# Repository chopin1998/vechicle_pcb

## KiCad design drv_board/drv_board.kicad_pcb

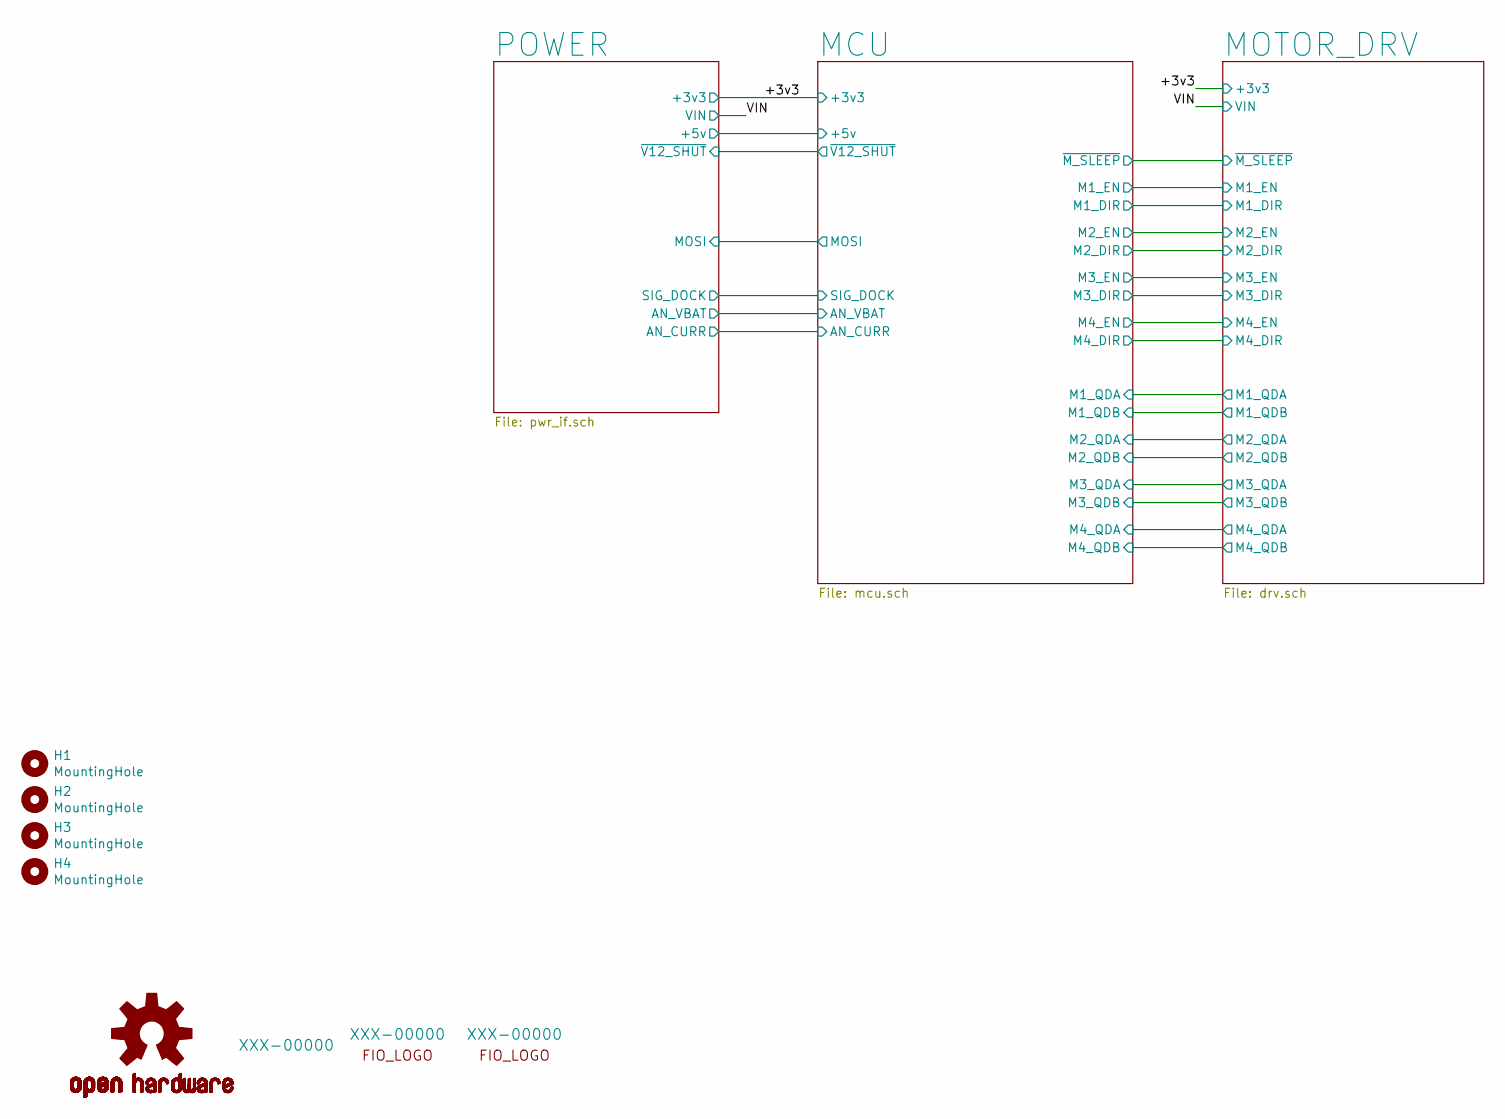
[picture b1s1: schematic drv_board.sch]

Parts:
H1, H2, H3, H4: MountingHole; MountingHole_3.2mm_M3_ISO14580
LOGO1: OSHW-LOGOL; OSHW-Logo2_7.3x6mm_SilkScreen
LOGO2: FIO_LOGOV2; KiCad-Logo2_5mm_SilkScreen
LOGO3: FIO_LOGOV2; ESD-Logo_6.6x6mm_SilkScreen

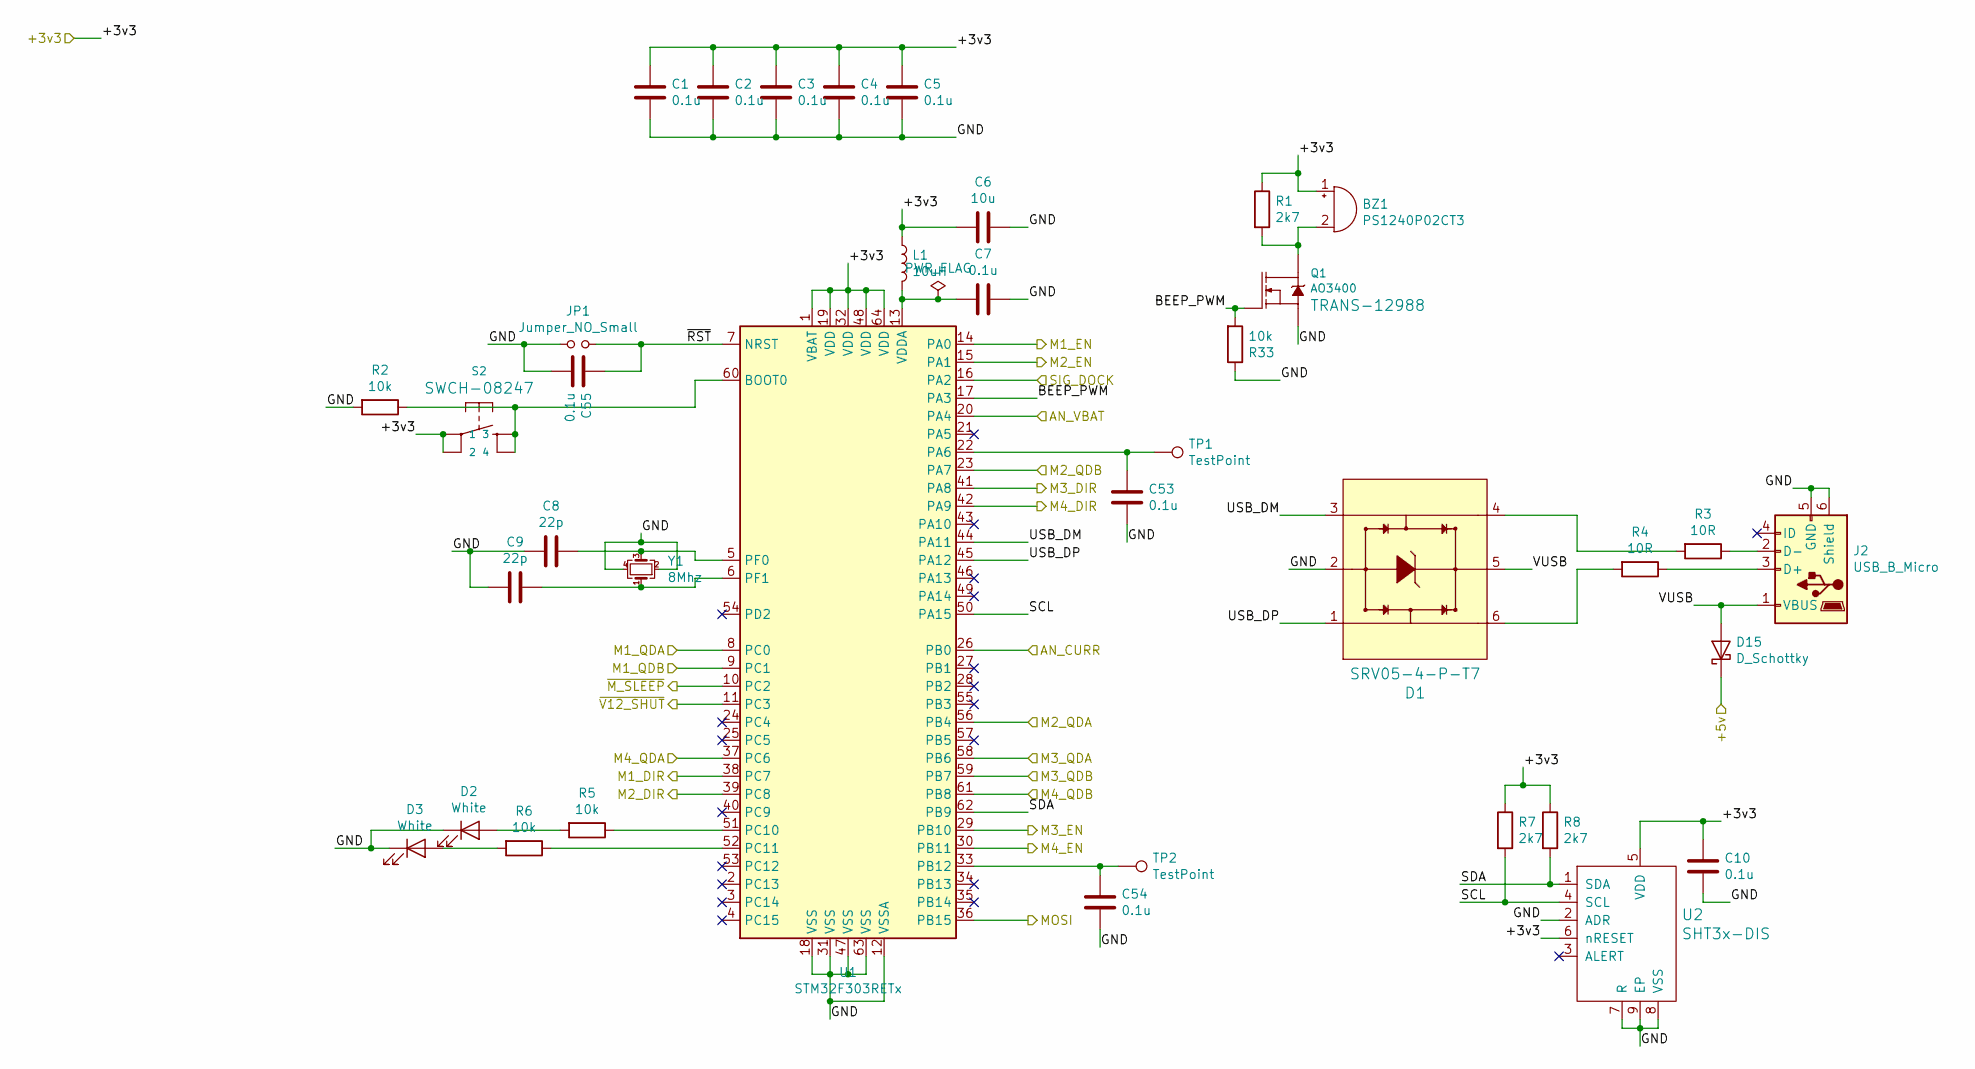
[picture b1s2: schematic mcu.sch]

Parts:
BZ1: PS1240P02CT3; Buzzer_12x9.5RM7.6
C1, C2, C3, C4, C5, C7, C10, C53, C54, C55: 0.1u; C_0402_1005Metric
C6: 10u; C_0402_1005Metric
C8, C9: 22p; C_0402_1005Metric
D1: SRV05-4-P-T7; SOT23-6L; MPN USBLC6-2SC6; Digi-Key_PN 497-5235-1-ND
D2, D3: White; LED_0603_1608Metric
D15: D_Schottky; D_SOD-123F
J2: USB_B_Micro; USB_Micro-B_Wuerth_629105150521
JP1: Jumper_NO_Small; PinHeader_1x02_P1.27mm_Vertical
L1: 10uH; L_0603_1608Metric
Q1: AO3400; SOT-23
R1, R7, R8: 2k7; R_0402_1005Metric
R2, R5, R6, R33: 10k; R_0402_1005Metric
R3, R4: 10R; R_0402_1005Metric
S2: MOMENTARY-SWITCH-SPST-2-SMD-5.2MM; TACTILE_SWITCH_SMD_5.2MM
TP1, TP2: TestPoint; TestPoint_Pad_D1.0mm
U1: STM32F303RETx; LQFP-64_10x10mm_P0.5mm
U2: SHT3x-DIS; DFN-8-1EP_2x2mm_P0.5mm_EP0.9x1.5mm
Y1: 8Mhz; Crystal_SMD_SeikoEpson_TSX3225-4Pin_3.2x2.5mm

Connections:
/+3v3: BZ1.1 (-), C1.1, C2.1, C3.1, C4.1, C5.1, C6.2, C10.1, L1.1, R1.1, R7.1, R8.1, S2.1, S2.2, U1.1 (VBAT), U1.19 (VDD), U1.32 (VDD), U1.48 (VDD), U1.64 (VDD), U2.5 (VDD), U2.6 (nRESET); also elsewhere on the board
/MCU/+5v: D15.1 (K); also elsewhere on the board
/MCU/AN_CURR: U1.26 (PB0); also elsewhere on the board
/MCU/AN_VBAT: U1.20 (PA4); also elsewhere on the board
/MCU/BEEP_PWM: Q1.1 (G), R33.2, U1.17 (PA3)
/MCU/M1_DIR: U1.38 (PC7); also elsewhere on the board
/MCU/M1_EN: U1.14 (PA0); also elsewhere on the board
/MCU/M1_QDA: U1.8 (PC0); also elsewhere on the board
/MCU/M1_QDB: U1.9 (PC1); also elsewhere on the board
/MCU/M2_DIR: U1.39 (PC8); also elsewhere on the board
/MCU/M2_EN: U1.15 (PA1); also elsewhere on the board
/MCU/M2_QDA: U1.56 (PB4); also elsewhere on the board
/MCU/M2_QDB: U1.23 (PA7); also elsewhere on the board
/MCU/M3_DIR: U1.41 (PA8); also elsewhere on the board
/MCU/M3_EN: U1.29 (PB10); also elsewhere on the board
/MCU/M3_QDA: U1.58 (PB6); also elsewhere on the board
/MCU/M3_QDB: U1.59 (PB7); also elsewhere on the board
/MCU/M4_DIR: U1.42 (PA9); also elsewhere on the board
/MCU/M4_EN: U1.30 (PB11); also elsewhere on the board
/MCU/M4_QDA: U1.37 (PC6); also elsewhere on the board
/MCU/M4_QDB: U1.61 (PB8); also elsewhere on the board
/MCU/MOSI: U1.36 (PB15); also elsewhere on the board
/MCU/SCL: R7.2, U1.50 (PA15), U2.4 (SCL)
/MCU/SDA: R8.2, U1.62 (PB9), U2.1 (SDA)
/MCU/SIG_DOCK: U1.16 (PA2); also elsewhere on the board
/MCU/USB_DM: D1.3, U1.44 (PA11)
/MCU/USB_DP: D1.1, U1.45 (PA12)
/MCU/VUSB: D1.5, D15.2 (A), J2.1 (VBUS)
/MCU/~M_SLEEP: U1.10 (PC2); also elsewhere on the board
/MCU/~RST: C55.1, JP1.2, U1.7 (NRST)
/MCU/~V12_SHUT: U1.11 (PC3); also elsewhere on the board
GND: C1.2, C2.2, C3.2, C4.2, C5.2, C6.1, C7.1, C8.2, C9.2, C10.2, C53.2, C54.2, C55.2, D1.2, D2.1 (K), D3.1 (K), J2.5 (GND), J2.6 (Shield), JP1.1, Q1.2 (S), R2.2, R33.1, U1.12 (VSSA), U1.18 (VSS), U1.31 (VSS), U1.47 (VSS), U1.63 (VSS), U2.2 (ADR), U2.7 (R), U2.8 (VSS), U2.9 (EP), Y1.2, Y1.4; also elsewhere on the board
unnamed: BZ1.2 (+), Q1.3 (D), R1.2
unnamed: C7.2, L1.2, U1.13 (VDDA)
unnamed: C8.1, U1.5 (PF0), Y1.3
unnamed: C9.1, U1.6 (PF1), Y1.1
unnamed: C53.1, TP1.1, U1.22 (PA6)
unnamed: C54.1, TP2.1, U1.33 (PB12)
unnamed: D1.4, R3.2
unnamed: D1.6, R4.2
unnamed: D2.2 (A), R5.2
unnamed: D3.2 (A), R6.2
unnamed: J2.2 (D-), R3.1
unnamed: J2.3 (D+), R4.1
unnamed: R2.1, S2.3, S2.4, U1.60 (BOOT0)
unnamed: R5.1, U1.51 (PC10)
unnamed: R6.1, U1.52 (PC11)

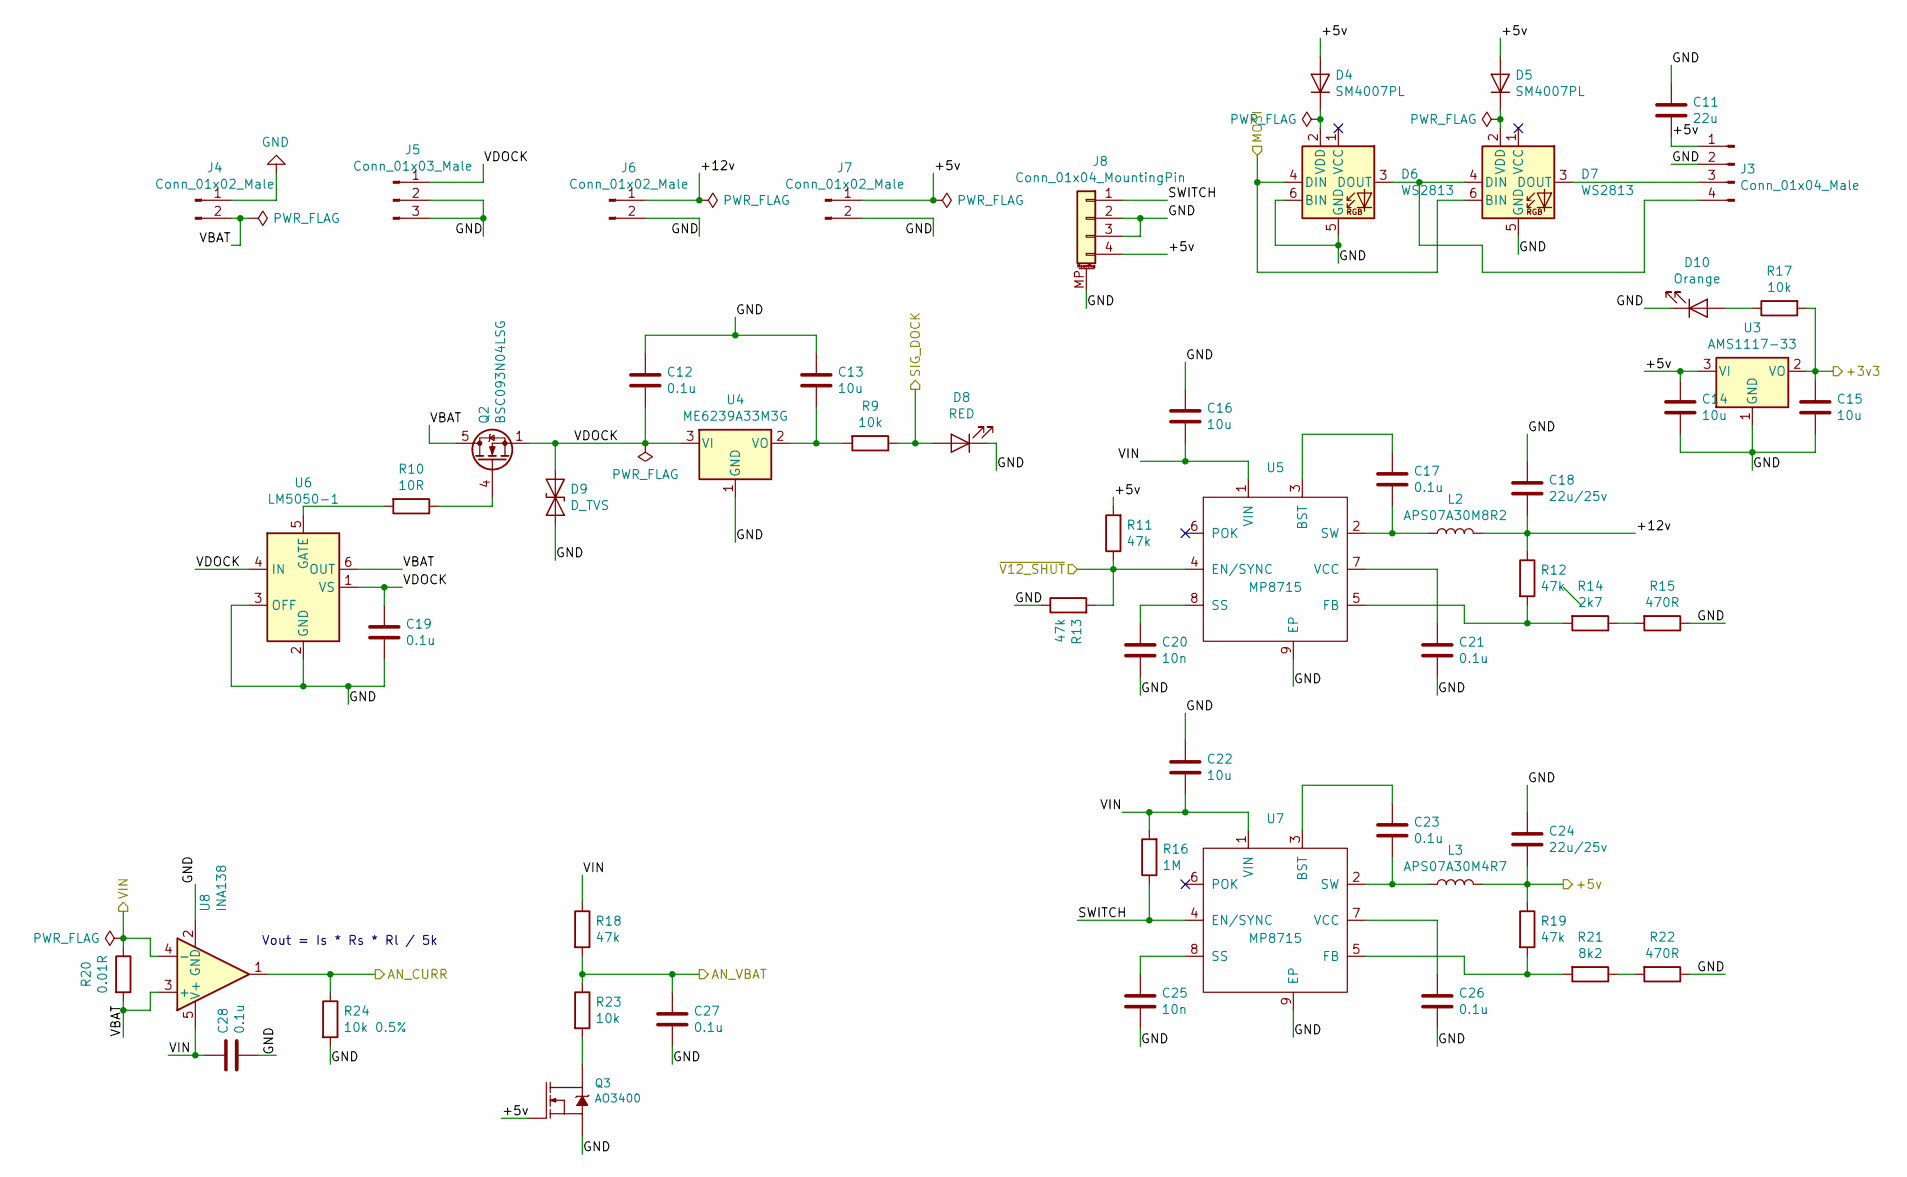
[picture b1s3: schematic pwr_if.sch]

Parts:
C11: 22u; C_0805_2012Metric
C12, C17, C19, C21, C23, C26, C27, C28: 0.1u; C_0402_1005Metric
C13, C14, C15: 10u; C_0402_1005Metric
C16, C22: 10u; C_0603_1608Metric
C18, C24: 22u/25v; C_0805_2012Metric
C20, C25: 10n; C_0402_1005Metric
D4, D5: SM4007PL; D_SOD-123F
D6, D7: WS2813; LED_WS2812_PLCC6_5.0x5.0mm_P1.6mm
D8: RED; LED_0603_1608Metric
D9: D_TVS; D_SMA
D10: Orange; LED_0603_1608Metric
J3: Conn_01x04_Male; JST_XH_B4B-XH-A_1x04_P2.50mm_Vertical
J4: Conn_01x02_Male; AMASS_XT30PW-F_1x02_P2.50mm_Horizontal
J5: Conn_01x03_Male; JST_XH_B3B-XH-A_1x03_P2.50mm_Vertical
J6: Conn_01x02_Male; JST_XH_B2B-XH-A_1x02_P2.50mm_Vertical
J7: Conn_01x02_Male; JST_PH_B2B-PH-K_1x02_P2.00mm_Vertical
J8: Conn_01x04_MountingPin; JST_SH_BM04B-SRSS-TB_1x04-1MP_P1.00mm_Vertical
L2: APS07A30M8R2; L_7.3x7.3_H3.5
L3: APS07A30M4R7; L_7.3x7.3_H3.5
Q2: BSC093N04LSG; TDSON-8-1
Q3: AO3400; SOT-23
R9, R17, R23: 10k; R_0402_1005Metric
R10: 10R; R_0402_1005Metric
R11, R12, R13, R18, R19: 47k; R_0402_1005Metric
R14: 2k7; R_0402_1005Metric
R15, R22: 470R; R_0402_1005Metric
R16: 1M; R_0402_1005Metric
R20: 0.01R; R_2512_6332Metric
R21: 8k2; R_0402_1005Metric
R24: 10k 0.5%; R_0603_1608Metric
U3: AMS1117-33; SOT-223-3_TabPin2
U4: ME6239A33M3G; TSOT-23
U5, U7: MP8715; SOIC-8-1EP_3.9x4.9mm_P1.27mm_EP2.514x3.2mm
U6: LM5050-1; TSOT-23-6
U8: INA138; SOT-23-5

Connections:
/+3v3: C15.1, R17.2, U3.2 (VO); also elsewhere on the board
/MCU/+5v: C11.2, C14.1, C24.1, D4.2 (A), D5.2 (A), J3.1, J7.1, J8.4, L3.2, Q3.1 (G), R11.2, R19.1, U3.3 (VI); also elsewhere on the board
/MCU/AN_CURR: R24.1, U8.1; also elsewhere on the board
/MCU/AN_VBAT: C27.2, R18.2, R23.1; also elsewhere on the board
/MCU/MOSI: D6.4 (DIN), D7.6 (BIN); also elsewhere on the board
/MCU/SIG_DOCK: D8.2 (A), R9.1; also elsewhere on the board
/MCU/~V12_SHUT: R11.1, R13.2, U5.4 (EN/SYNC); also elsewhere on the board
/POWER/+12v: C18.1, J6.1, L2.2, R12.1
/POWER/SWITCH: J8.1, R16.1, U7.4 (EN/SYNC)
/POWER/VBAT: J4.2, Q2.5 (D), R20.2, U6.6 (OUT), U8.3 (+)
/POWER/VDOCK: C12.2, C19.1, D9.1 (A1), J5.1, Q2.1 (S), Q2.2 (S), Q2.3 (S), U4.3 (VI), U6.1 (VS), U6.4 (IN)
GND: C11.1, C12.1, C13.1, C14.2, C15.2, C16.1, C18.2, C19.2, C20.1, C21.1, C22.1, C24.2, C25.1, C26.1, C27.1, C28.1, D6.5 (GND), D6.6 (BIN), D7.5 (GND), D8.1 (K), D9.2 (A2), D10.1 (K), J3.2, J4.1, J5.2, J5.3, J6.2, J7.2, J8.2, J8.3, J8.MP (MountPin), Q3.2 (S), R13.1, R15.1, R22.1, R24.2, U3.1 (GND), U4.1 (GND), U5.9 (EP), U6.2 (GND), U6.3 (OFF), U7.9 (EP), U8.2 (GND); also elsewhere on the board
unnamed: C13.2, R9.2, U4.2 (VO)
unnamed: C17.1, L2.1, U5.2 (SW)
unnamed: C17.2, U5.3 (BST)
unnamed: C20.2, U5.8 (SS)
unnamed: C21.2, U5.7 (VCC)
unnamed: C23.1, L3.1, U7.2 (SW)
unnamed: C23.2, U7.3 (BST)
unnamed: C25.2, U7.8 (SS)
unnamed: C26.2, U7.7 (VCC)
unnamed: D4.1 (K), D6.2 (VDD)
unnamed: D5.1 (K), D7.2 (VDD)
unnamed: D6.3 (DOUT), D7.4 (DIN), J3.4
unnamed: D7.3 (DOUT), J3.3
unnamed: D10.2 (A), R17.1
unnamed: Q2.4 (G), R10.1
unnamed: Q3.3 (D), R23.2
unnamed: R10.2, U6.5 (GATE)
unnamed: R12.2, R14.2, U5.5 (FB)
unnamed: R14.1, R15.2
unnamed: R19.2, R21.2, U7.5 (FB)
unnamed: R21.1, R22.2
VIN: C16.2, C22.2, C28.2, R16.2, R18.1, R20.1, U5.1 (VIN), U7.1 (VIN), U8.4 (-), U8.5 (V+); also elsewhere on the board

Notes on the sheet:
Vout = Is * Rs * Rl / 5k

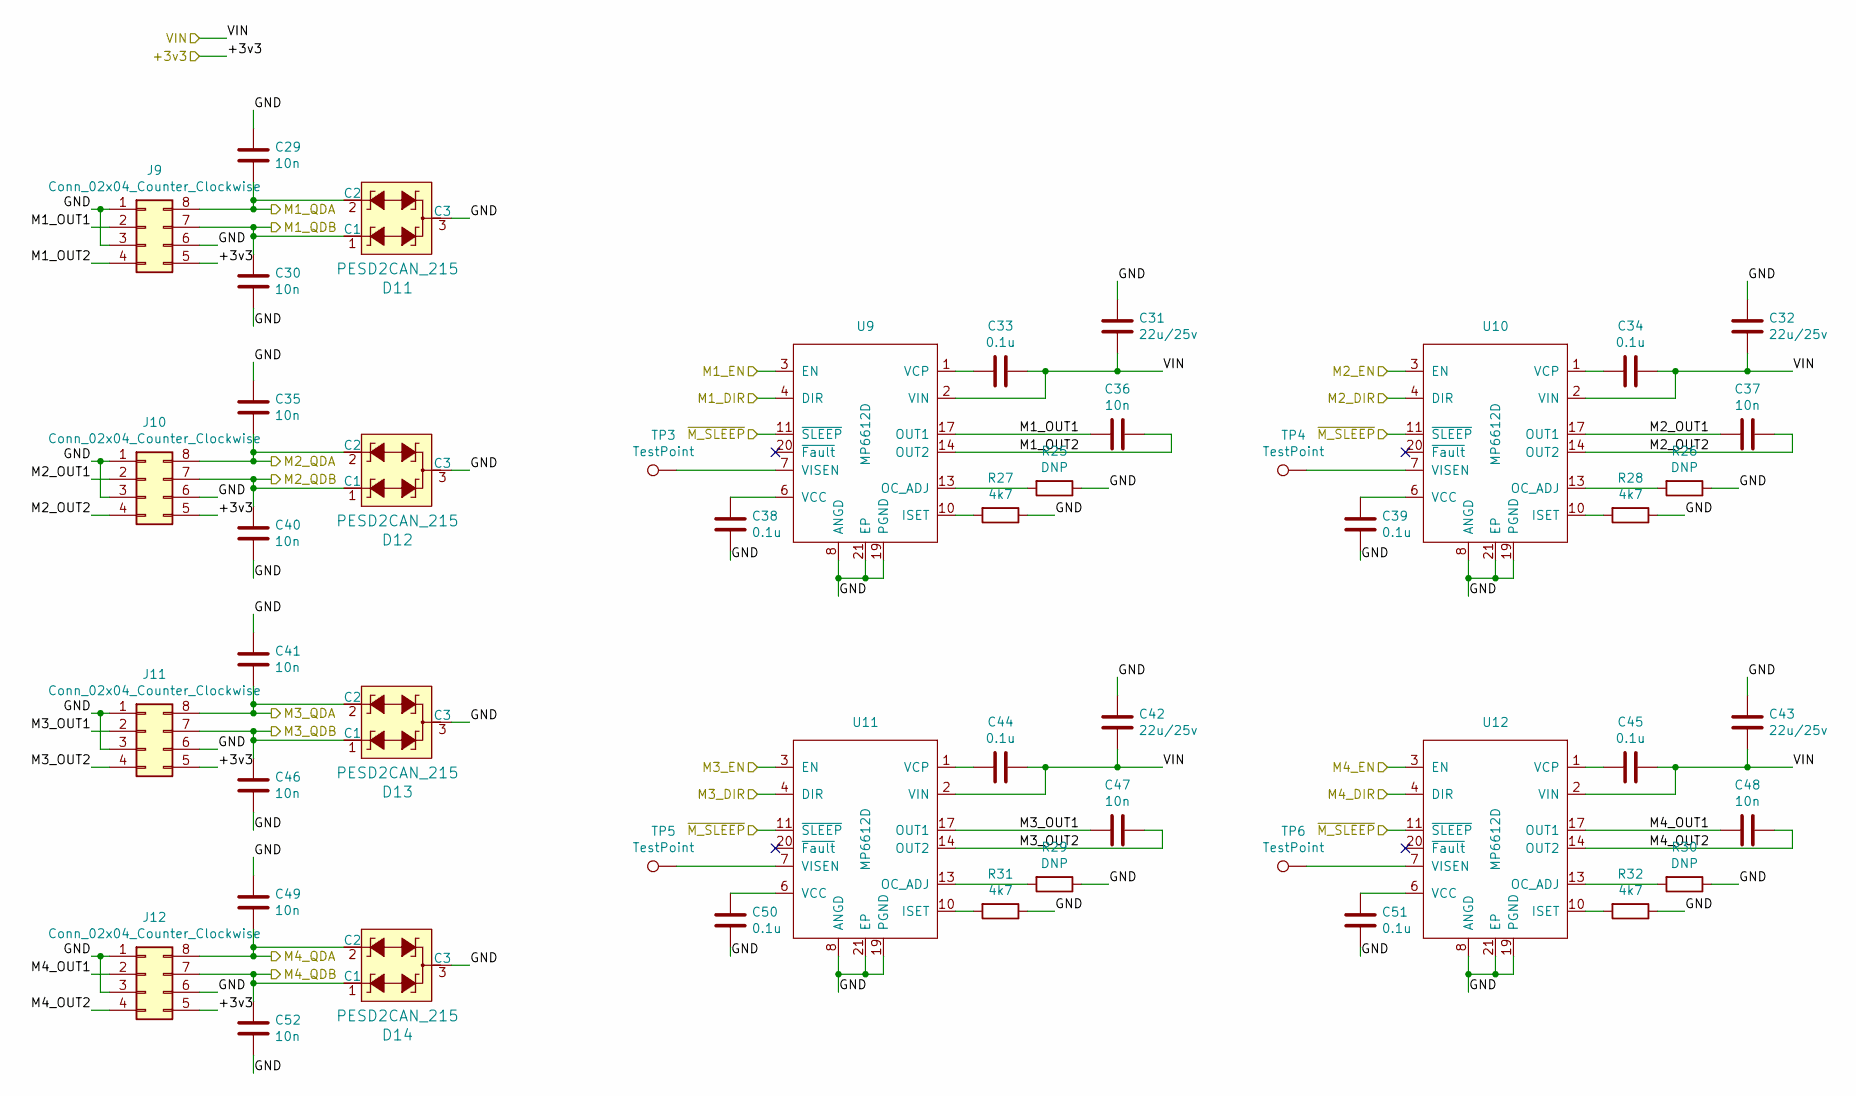
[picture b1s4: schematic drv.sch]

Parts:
C29, C30, C35, C36, C37, C40, C41, C46, C47, C48, C49, C52: 10n; C_0402_1005Metric
C31, C32, C42, C43: 22u/25v; C_0805_2012Metric
C33, C34, C38, C39, C44, C45, C50, C51: 0.1u; C_0402_1005Metric
D11, D12, D13, D14: PESD2CAN_215; SOT-23; MPN PESD2CAN,215; Digi-Key_PN 1727-3891-1-ND
J9, J10, J11, J12: Conn_02x04_Counter_Clockwise; JST_PHD_B8B-PHDSS_2x04_P2.00mm_Vertical
R25, R26, R29, R30: DNP; R_0201_0603Metric
R27, R28, R31, R32: 4k7; R_0402_1005Metric
TP3, TP4, TP5, TP6: TestPoint; TestPoint_Pad_D1.0mm
U9, U10, U11, U12: MP6612D; ETSSOP-20-1EP_4.4x6.5mm_P0.65mm_EP3x4.2mm

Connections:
/+3v3: J9.5, J10.5, J11.5, J12.5; also elsewhere on the board
/MCU/M1_DIR: U9.4 (DIR); also elsewhere on the board
/MCU/M1_EN: U9.3 (EN); also elsewhere on the board
/MCU/M1_QDA: C29.2, D11.2 (C2), J9.8; also elsewhere on the board
/MCU/M1_QDB: C30.1, D11.1 (C1), J9.7; also elsewhere on the board
/MCU/M2_DIR: U10.4 (DIR); also elsewhere on the board
/MCU/M2_EN: U10.3 (EN); also elsewhere on the board
/MCU/M2_QDA: C35.2, D12.2 (C2), J10.8; also elsewhere on the board
/MCU/M2_QDB: C40.1, D12.1 (C1), J10.7; also elsewhere on the board
/MCU/M3_DIR: U11.4 (DIR); also elsewhere on the board
/MCU/M3_EN: U11.3 (EN); also elsewhere on the board
/MCU/M3_QDA: C41.2, D13.2 (C2), J11.8; also elsewhere on the board
/MCU/M3_QDB: C46.1, D13.1 (C1), J11.7; also elsewhere on the board
/MCU/M4_DIR: U12.4 (DIR); also elsewhere on the board
/MCU/M4_EN: U12.3 (EN); also elsewhere on the board
/MCU/M4_QDA: C49.2, D14.2 (C2), J12.8; also elsewhere on the board
/MCU/M4_QDB: C52.1, D14.1 (C1), J12.7; also elsewhere on the board
/MCU/~M_SLEEP: U9.11 (~SLEEP), U10.11 (~SLEEP), U11.11 (~SLEEP), U12.11 (~SLEEP); also elsewhere on the board
/MOTOR_DRV/M1_OUT1: C36.2, J9.2, U9.17 (OUT1), U9.18 (OUT1)
/MOTOR_DRV/M1_OUT2: C36.1, J9.4, U9.14 (OUT2), U9.15 (OUT2)
/MOTOR_DRV/M2_OUT1: C37.2, J10.2, U10.17 (OUT1), U10.18 (OUT1)
/MOTOR_DRV/M2_OUT2: C37.1, J10.4, U10.14 (OUT2), U10.15 (OUT2)
/MOTOR_DRV/M3_OUT1: C47.2, J11.2, U11.17 (OUT1), U11.18 (OUT1)
/MOTOR_DRV/M3_OUT2: C47.1, J11.4, U11.14 (OUT2), U11.15 (OUT2)
/MOTOR_DRV/M4_OUT1: C48.2, J12.2, U12.17 (OUT1), U12.18 (OUT1)
/MOTOR_DRV/M4_OUT2: C48.1, J12.4, U12.14 (OUT2), U12.15 (OUT2)
GND: C29.1, C30.2, C31.1, C32.1, C35.1, C38.2, C39.2, C40.2, C41.1, C42.1, C43.1, C46.2, C49.1, C50.2, C51.2, C52.2, D11.3 (C3), D12.3 (C3), D13.3 (C3), D14.3 (C3), J9.1, J9.3, J9.6, J10.1, J10.3, J10.6, J11.1, J11.3, J11.6, J12.1, J12.3, J12.6, R25.1, R26.1, R27.1, R28.1, R29.1, R30.1, R31.1, R32.1, U9.8 (ANGD), U9.12 (PGND), U9.16 (PGND), U9.19 (PGND), U9.21 (EP), U10.8 (ANGD), U10.12 (PGND), U10.16 (PGND), U10.19 (PGND), U10.21 (EP), U11.8 (ANGD), U11.12 (PGND), U11.16 (PGND), U11.19 (PGND), U11.21 (EP), U12.8 (ANGD), U12.12 (PGND), U12.16 (PGND), U12.19 (PGND), U12.21 (EP); also elsewhere on the board
unnamed: C33.1, U9.1 (VCP)
unnamed: C34.1, U10.1 (VCP)
unnamed: C38.1, U9.6 (VCC)
unnamed: C39.1, U10.6 (VCC)
unnamed: C44.1, U11.1 (VCP)
unnamed: C45.1, U12.1 (VCP)
unnamed: C50.1, U11.6 (VCC)
unnamed: C51.1, U12.6 (VCC)
unnamed: R25.2, U9.13 (OC_ADJ)
unnamed: R26.2, U10.13 (OC_ADJ)
unnamed: R27.2, U9.10 (ISET)
unnamed: R28.2, U10.10 (ISET)
unnamed: R29.2, U11.13 (OC_ADJ)
unnamed: R30.2, U12.13 (OC_ADJ)
unnamed: R31.2, U11.10 (ISET)
unnamed: R32.2, U12.10 (ISET)
unnamed: TP3.1, U9.7 (VISEN)
unnamed: TP4.1, U10.7 (VISEN)
unnamed: TP5.1, U11.7 (VISEN)
unnamed: TP6.1, U12.7 (VISEN)
VIN: C31.2, C32.2, C33.2, C34.2, C42.2, C43.2, C44.2, C45.2, U9.2 (VIN), U9.5 (VIN), U9.9 (VIN), U10.2 (VIN), U10.5 (VIN), U10.9 (VIN), U11.2 (VIN), U11.5 (VIN), U11.9 (VIN), U12.2 (VIN), U12.5 (VIN), U12.9 (VIN); also elsewhere on the board

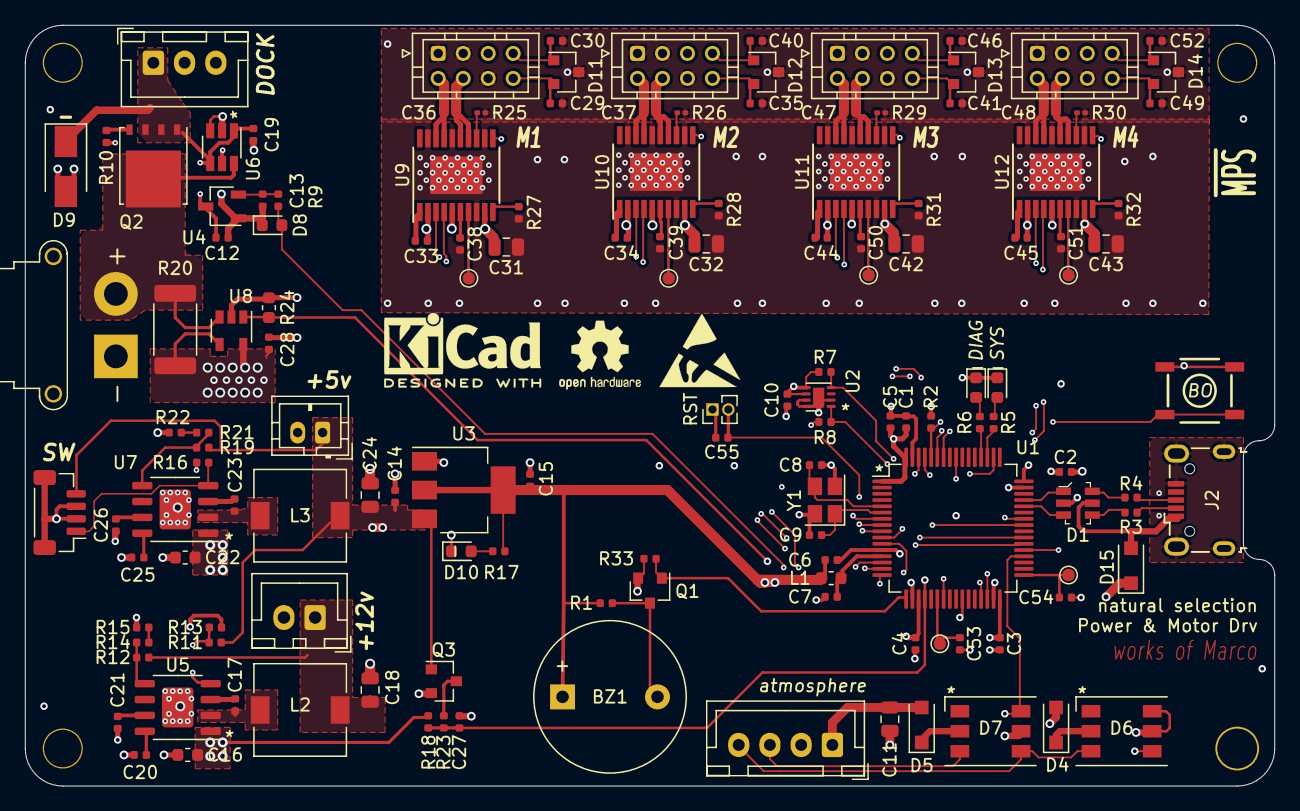
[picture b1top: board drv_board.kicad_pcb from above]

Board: 4 copper layers, 100.0 x 60.9 mm, 149 parts (0 on the bottom side), 101 nets.

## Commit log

2020-06-14 backup
